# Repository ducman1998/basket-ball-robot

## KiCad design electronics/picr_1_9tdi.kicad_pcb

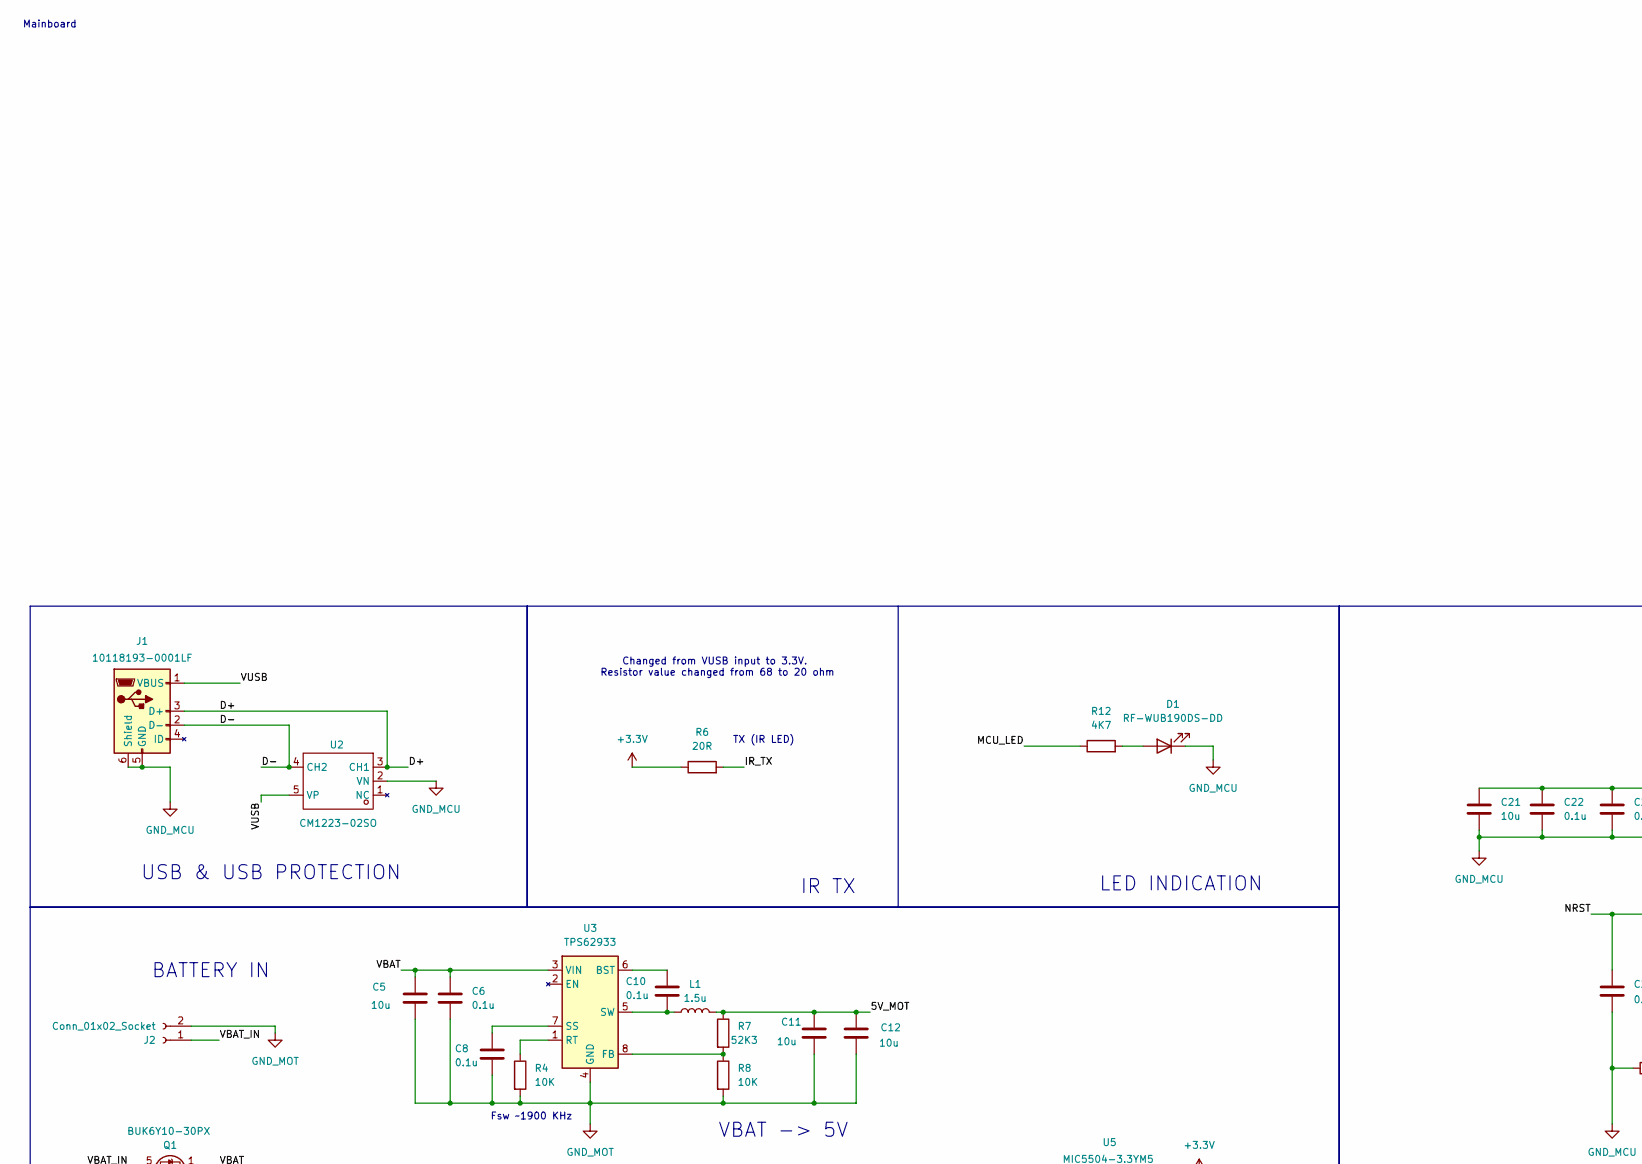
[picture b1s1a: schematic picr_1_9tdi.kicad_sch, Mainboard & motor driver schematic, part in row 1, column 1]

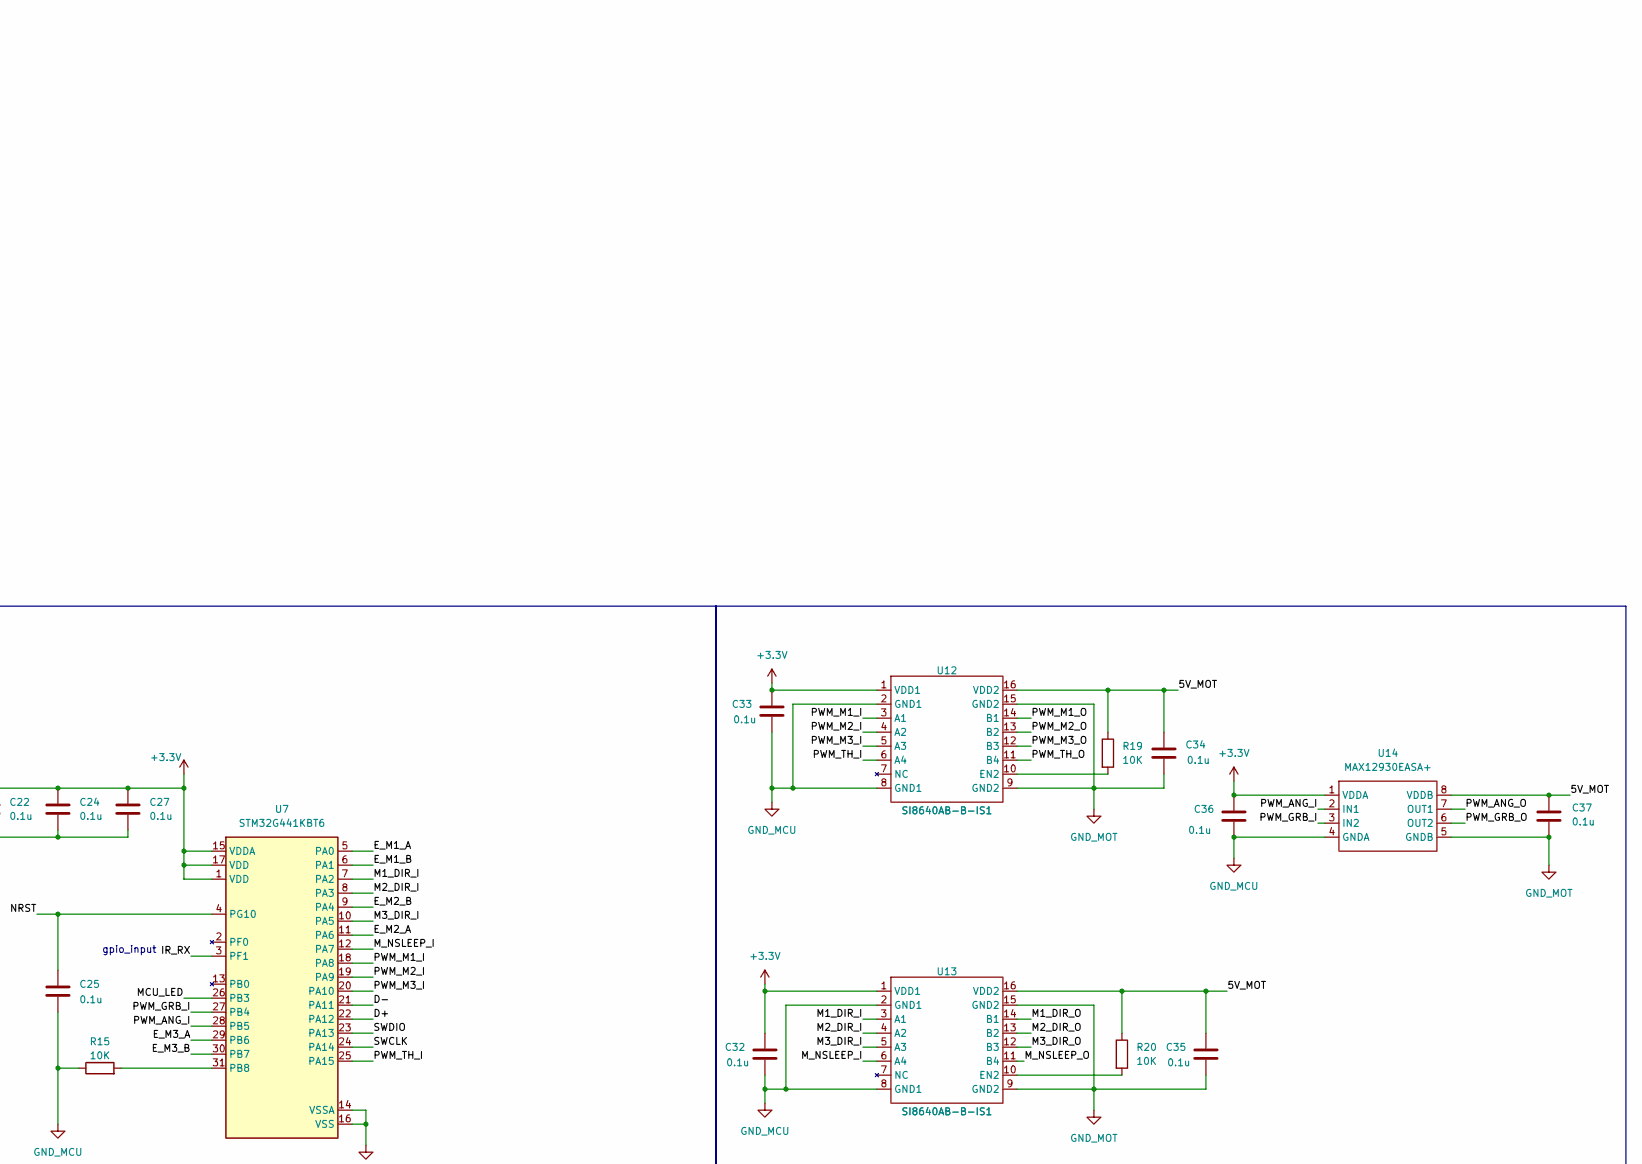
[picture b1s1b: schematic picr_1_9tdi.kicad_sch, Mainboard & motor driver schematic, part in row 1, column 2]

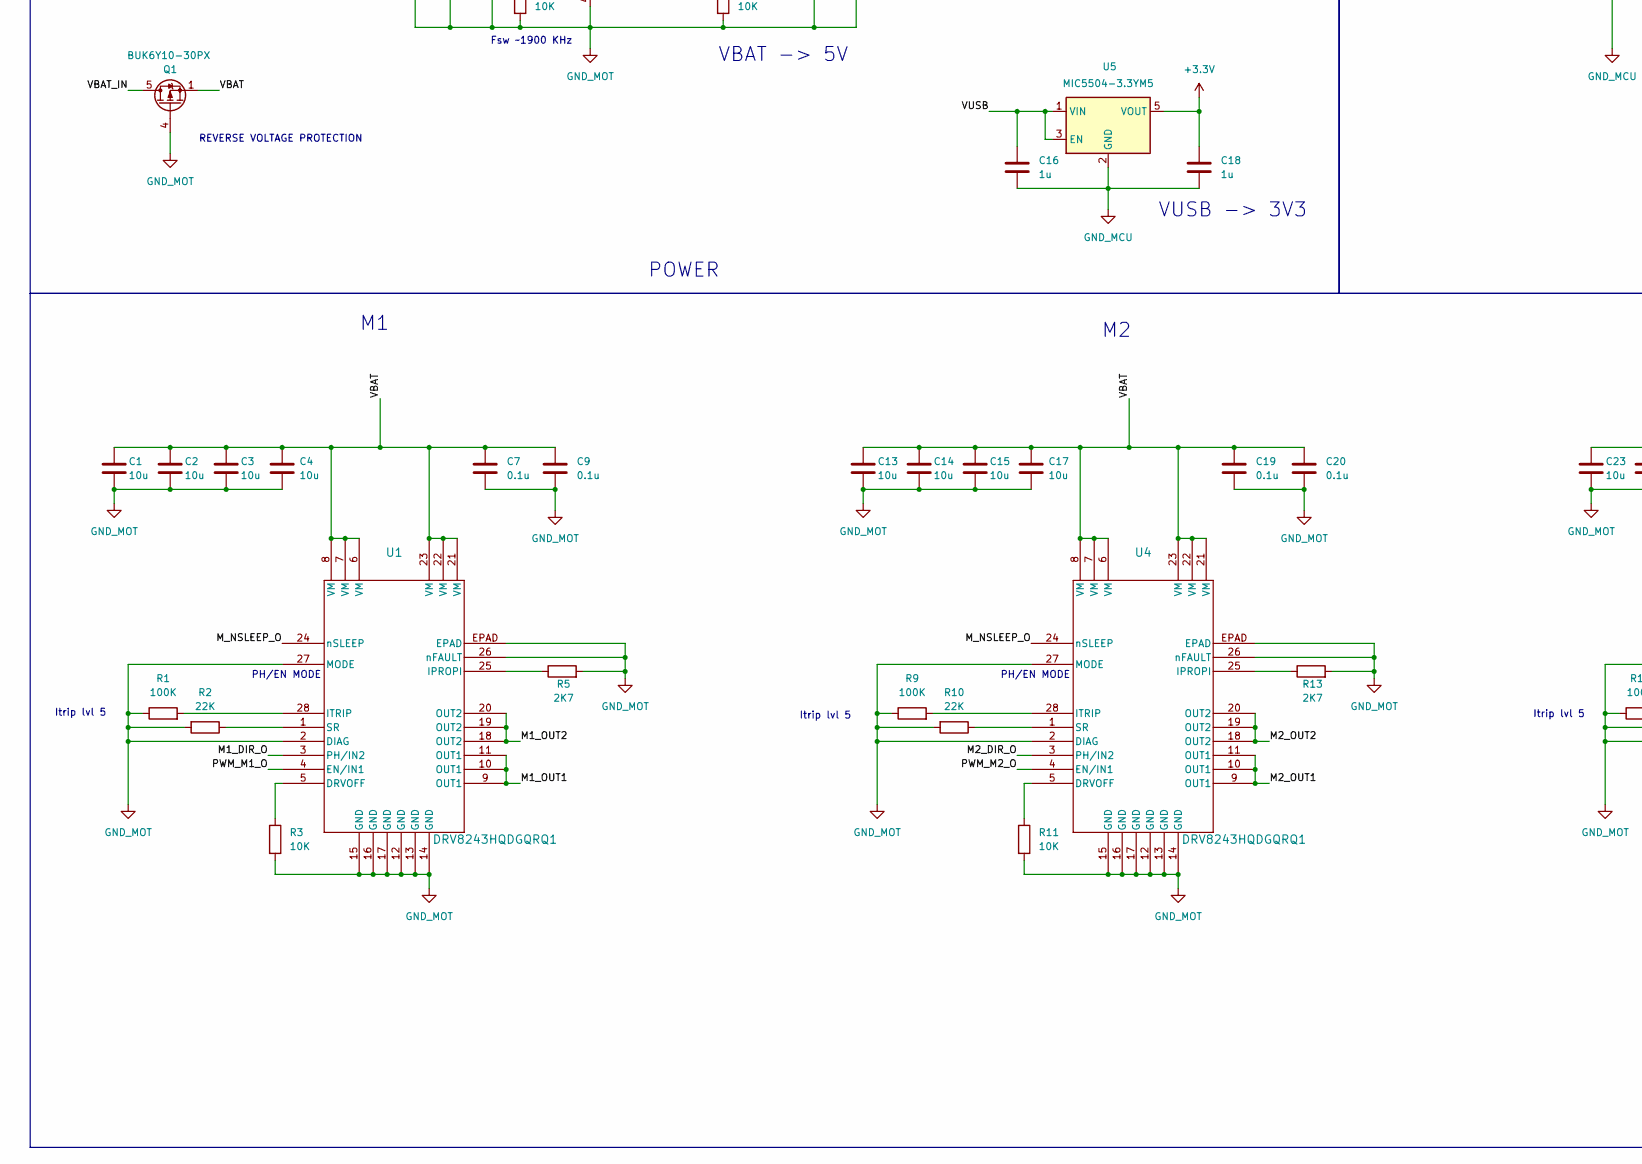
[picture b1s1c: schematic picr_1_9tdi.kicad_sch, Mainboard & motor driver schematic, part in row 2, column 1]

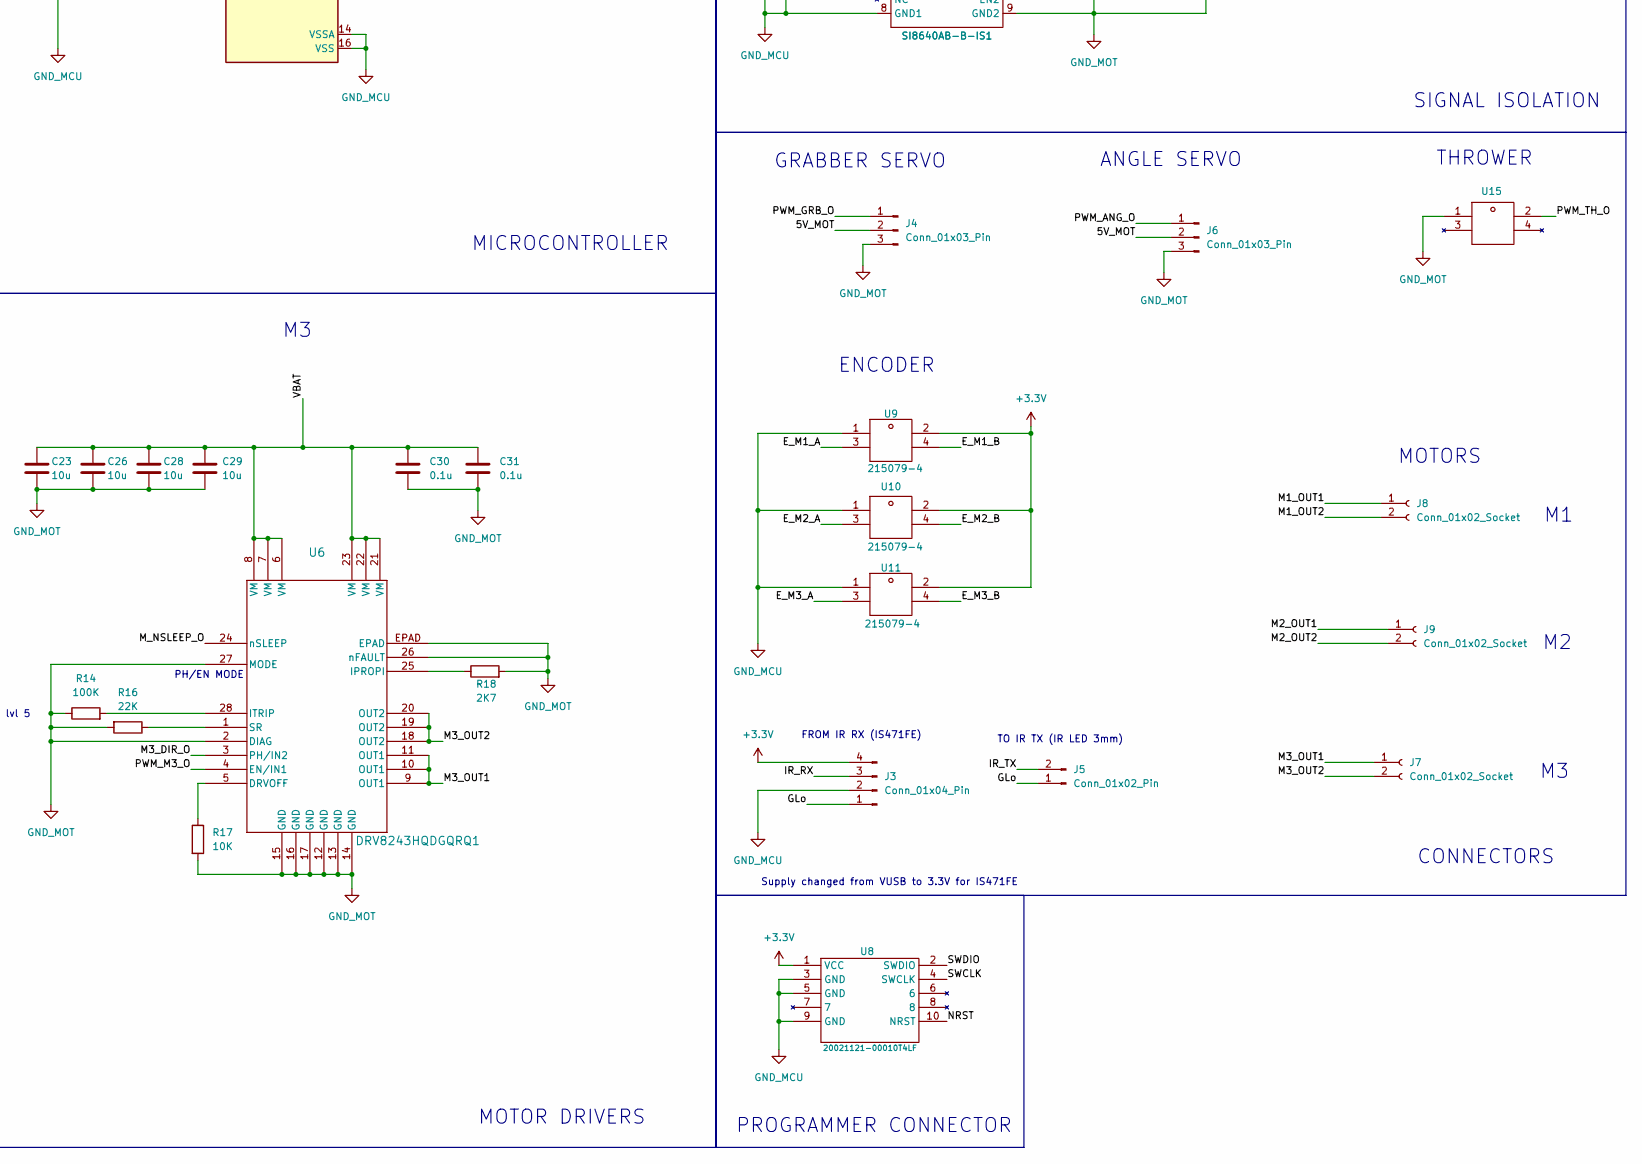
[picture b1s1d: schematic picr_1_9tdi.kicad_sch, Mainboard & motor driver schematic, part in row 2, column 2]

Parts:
C1, C2, C3, C4, C5, C13, C14, C15, C17, C21, C23, C26, C28, C29: 10u; C_0805_2012Metric_Pad1.18x1.45mm_HandSolder
C6, C7, C8, C9, C10, C19, C20, C22, C24, C25, C27, C30, C31, C32, C33, C34, C35, C36, C37: 0.1u; C_0603_1608Metric_Pad1.08x0.95mm_HandSolder
C11, C12: 10u; C_0603_1608Metric_Pad1.08x0.95mm_HandSolder
C16, C18: 1u; C_0603_1608Metric_Pad1.08x0.95mm_HandSolder
D1: RF-WUB190DS-DD; LED_0603_1608Metric_Pad1.05x0.95mm_HandSolder
J1: 10118193-0001LF; USB_Micro-B_Amphenol_10118193-0001LF_Horizontal
J2: Conn_01x02_Socket; SolderWirePad_1x02_SMD_3x4mm_power
J3: Conn_01x04_Pin; PinHeader_1x04_P2.54mm_Vertical
J4, J6: Conn_01x03_Pin; PinHeader_1x03_P2.54mm_Vertical
J5: Conn_01x02_Pin; PinHeader_1x02_P2.54mm_Vertical
J7, J8, J9: Conn_01x02_Socket; SolderWirePad_1x02_SMD_3x4mm
L1: 1.5u; SRP4021HMCT-1R5M_custom
Q1: BUK6Y10-30PX
R1, R9, R14: 100K; R_0603_1608Metric_Pad0.98x0.95mm_HandSolder
R2, R10, R16: 22K; R_0603_1608Metric_Pad0.98x0.95mm_HandSolder
R3, R4, R8, R11, R15, R17, R19, R20: 10K; R_0603_1608Metric_Pad0.98x0.95mm_HandSolder
R5, R13, R18: 2K7; R_0603_1608Metric_Pad0.98x0.95mm_HandSolder
R6: 20R; R_0603_1608Metric_Pad0.98x0.95mm_HandSolder
R7: 52K3; R_0603_1608Metric_Pad0.98x0.95mm_HandSolder
R12: 4K7; R_0603_1608Metric_Pad0.98x0.95mm_HandSolder
U1, U4, U6: DRV8243HQDGQRQ1; VSSOP_SDGQQ1_TEX-L
U2: CM1223-02SO; SOT-23-5_L2.9-W1.6-P0.95-LS2.8-BR; Manufacturer Part CM1223-02SO; LCSC Part Name CM1223-02SO
U3: TPS62933; SOT-583-8
U5: MIC5504-3.3YM5; SOT-23-5
U7: STM32G441KBT6; LQFP-32_7x7mm_P0.8mm
U8: 20021121-00010T4LF; HDR-SMD_10P-P1.27-V-M-R2-C5-S1.27-LS5.5; Manufacturer Part 20021121-00010T4LF; LCSC Part Name 间距:1.27mm 立贴
U9, U10, U11: 215079-4; TE_Micro-MaTch_215079-4_2x02_P1.27mm_Vertical; Manufacturer Part 215079-4; LCSC Part Name 215079-4
U12, U13: SI8640AB-B-IS1; Manufacturer Part SI8640AB-B-IS1; LCSC Part Name SI8640AB-B-IS1
U14: MAX12930EASA+; SOIC-8_L4.9-W3.9-P1.27-LS6.0-BL; Manufacturer Part MAX12930EASA+; LCSC Part Name MAX12930EASA+
U15: TE_Micro-MaTch_215079-4_2x02_P1.27mm_Vertical; Manufacturer Part 215079-4; LCSC Part Name 215079-4

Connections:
+3.3V: C18.1, C21.1, C22.1, C24.1, C27.1, C32.1, C33.1, C36.1, J3.4, R6.1, U5.5 (VOUT), U7.1 (VDD), U7.15 (VDDA), U7.17 (VDD), U8.1 (VCC), U9.2, U10.2, U11.2, U12.1 (VDD1), U13.1 (VDD1), U14.1 (VDDA)
/5V_MOT: C11.1, C12.1, C34.1, C35.1, C37.1, J4.2, J6.2, L1.2, R7.1, R19.1, R20.1, U12.16 (VDD2), U13.16 (VDD2), U14.8 (VDDB)
/D+: J1.3 (D+), U2.3 (CH1), U7.22 (PA12)
/D-: J1.2 (D-), U2.4 (CH2), U7.21 (PA11)
/E_M1_A: U7.5 (PA0), U9.3
/E_M1_B: U7.6 (PA1), U9.4
/E_M2_A: U7.11 (PA6), U10.3
/E_M2_B: U7.9 (PA4), U10.4
/E_M3_A: U7.29 (PB6), U11.3
/E_M3_B: U7.30 (PB7), U11.4
/GLo: J3.1, J5.1
/IR_RX: J3.3, U7.3 (PF1)
/IR_TX: J5.2, R6.2
/M1_DIR_I: U7.7 (PA2), U13.3 (A1)
/M1_DIR_O: U1.3 (PH/IN2), U13.14 (B1)
/M1_OUT1: J8.1, U1.9 (OUT1), U1.10 (OUT1), U1.11 (OUT1)
/M1_OUT2: J8.2, U1.18 (OUT2), U1.19 (OUT2), U1.20 (OUT2)
/M2_DIR_I: U7.8 (PA3), U13.4 (A2)
/M2_DIR_O: U4.3 (PH/IN2), U13.13 (B2)
/M2_OUT1: J9.1, U4.9 (OUT1), U4.10 (OUT1), U4.11 (OUT1)
/M2_OUT2: J9.2, U4.18 (OUT2), U4.19 (OUT2), U4.20 (OUT2)
/M3_DIR_I: U7.10 (PA5), U13.5 (A3)
/M3_DIR_O: U6.3 (PH/IN2), U13.12 (B3)
/M3_OUT1: J7.1, U6.9 (OUT1), U6.10 (OUT1), U6.11 (OUT1)
/M3_OUT2: J7.2, U6.18 (OUT2), U6.19 (OUT2), U6.20 (OUT2)
/MCU_LED: R12.1, U7.26 (PB3)
/M_NSLEEP_I: U7.12 (PA7), U13.6 (A4)
/M_NSLEEP_O: U1.24 (nSLEEP), U4.24 (nSLEEP), U6.24 (nSLEEP), U13.11 (B4)
/NRST: C25.1, U7.4 (PG10), U8.10 (NRST)
/PWM_ANG_I: U7.28 (PB5), U14.2 (IN1)
/PWM_ANG_O: J6.1, U14.7 (OUT1)
/PWM_GRB_I: U7.27 (PB4), U14.3 (IN2)
/PWM_GRB_O: J4.1, U14.6 (OUT2)
/PWM_M1_I: U7.18 (PA8), U12.3 (A1)
/PWM_M1_O: U1.4 (EN/IN1), U12.14 (B1)
/PWM_M2_I: U7.19 (PA9), U12.4 (A2)
/PWM_M2_O: U4.4 (EN/IN1), U12.13 (B2)
/PWM_M3_I: U7.20 (PA10), U12.5 (A3)
/PWM_M3_O: U6.4 (EN/IN1), U12.12 (B3)
/PWM_TH_I: U7.25 (PA15), U12.6 (A4)
/PWM_TH_O: U12.11 (B4), U15.2
/SWCLK: U7.24 (PA14), U8.4 (SWCLK)
/SWDIO: U7.23 (PA13), U8.2 (SWDIO)
/VBAT: C1.1, C2.1, C3.1, C4.1, C5.1, C6.1, C7.1, C9.1, C13.1, C14.1, C15.1, C17.1, C19.1, C20.1, C23.1, C26.1, C28.1, C29.1, C30.1, C31.1, Q1.1 (S), Q1.2 (S), Q1.3 (S), U1.6 (VM), U1.7 (VM), U1.8 (VM), U1.21 (VM), U1.22 (VM), U1.23 (VM), U3.3 (VIN), U4.6 (VM), U4.7 (VM), U4.8 (VM), U4.21 (VM), U4.22 (VM), U4.23 (VM), U6.6 (VM), U6.7 (VM), U6.8 (VM), U6.21 (VM), U6.22 (VM), U6.23 (VM)
/VBAT_IN: J2.1, Q1.5 (D)
/VUSB: C16.1, J1.1 (VBUS), U2.5 (VP), U5.1 (VIN), U5.3 (EN)
GND_MCU: C16.2, C18.2, C21.2, C22.2, C24.2, C25.2, C27.2, C32.2, C33.2, C36.2, D1.1 (K), J1.5 (GND), J1.6 (Shield), J3.2, R15.1, U2.2 (VN), U5.2 (GND), U7.14 (VSSA), U7.16 (VSS), U7.32 (VSS), U8.3 (GND), U8.5 (GND), U8.9 (GND), U9.1, U10.1, U11.1, U12.2 (GND1), U12.8 (GND1), U13.2 (GND1), U13.8 (GND1), U14.4 (GNDA)
GND_MOT: C1.2, C2.2, C3.2, C4.2, C5.2, C6.2, C7.2, C8.2, C9.2, C11.2, C12.2, C13.2, C14.2, C15.2, C17.2, C19.2, C20.2, C23.2, C26.2, C28.2, C29.2, C30.2, C31.2, C34.2, C35.2, C37.2, J2.2, J4.3, J6.3, Q1.4 (G), R1.1, R2.2, R3.2, R4.2, R5.2, R8.2, R9.1, R10.2, R11.2, R13.2, R14.1, R16.2, R17.2, R18.2, U1.2 (DIAG), U1.12 (GND), U1.13 (GND), U1.14 (GND), U1.15 (GND), U1.16 (GND), U1.17 (GND), U1.26 (nFAULT), U1.27 (MODE), U1.EPAD, U3.4 (GND), U4.2 (DIAG), U4.12 (GND), U4.13 (GND), U4.14 (GND), U4.15 (GND), U4.16 (GND), U4.17 (GND), U4.26 (nFAULT), U4.27 (MODE), U4.EPAD, U6.2 (DIAG), U6.12 (GND), U6.13 (GND), U6.14 (GND), U6.15 (GND), U6.16 (GND), U6.17 (GND), U6.26 (nFAULT), U6.27 (MODE), U6.EPAD, U12.9 (GND2), U12.15 (GND2), U13.9 (GND2), U13.15 (GND2), U14.5 (GNDB), U15.1
unnamed: D1.2 (A), R12.2
unnamed: R3.1, U1.5 (DRVOFF)
unnamed: R5.1, U1.25 (IPROPI)
unnamed: R1.2, U1.28 (ITRIP)
unnamed: R2.1, U1.1 (SR)
unnamed: C10.1, U3.6 (BST)
unnamed: R7.2, R8.1, U3.8 (FB)
unnamed: R4.1, U3.1 (RT)
unnamed: C8.1, U3.7 (SS)
unnamed: C10.2, L1.1, U3.5 (SW)
unnamed: R11.1, U4.5 (DRVOFF)
unnamed: R13.1, U4.25 (IPROPI)
unnamed: R9.2, U4.28 (ITRIP)
unnamed: R10.1, U4.1 (SR)
unnamed: R17.1, U6.5 (DRVOFF)
unnamed: R18.1, U6.25 (IPROPI)
unnamed: R14.2, U6.28 (ITRIP)
unnamed: R16.1, U6.1 (SR)
unnamed: R15.2, U7.31 (PB8)
unnamed: R19.2, U12.10 (EN2)
unnamed: R20.2, U13.10 (EN2)

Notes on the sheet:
PH/EN MODE
VUSB -> 3V3
THROWER
TO IR TX (IR LED 3mm)
Fsw ~1900 KHz
Itrip lvl 5
Supply changed from VUSB to 3.3V for IS471FE
gpio_input
GRABBER SERVO
POWER
VBAT -> 5V
REVERSE VOLTAGE PROTECTION
ANGLE SERVO
ENCODER
MOTOR DRIVERS
PROGRAMMER CONNECTOR
LED INDICATION
SIGNAL ISOLATION
IR TX
MOTORS
TX (IR LED)
FROM IR RX (IS471FE)
Changed from VUSB input to 3.3V. Resistor value changed from 68 to 20 ohm
MICROCONTROLLER
CONNECTORS
Mainboard
BATTERY IN
USB & USB PROTECTION

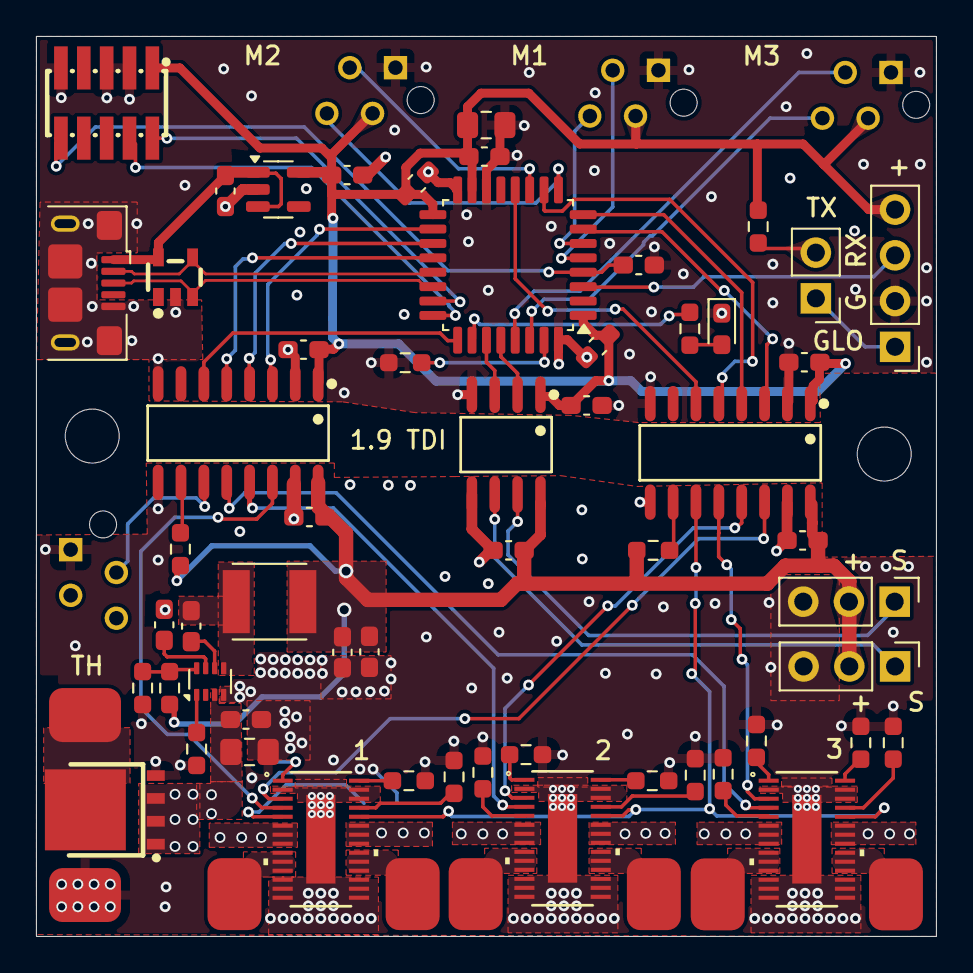
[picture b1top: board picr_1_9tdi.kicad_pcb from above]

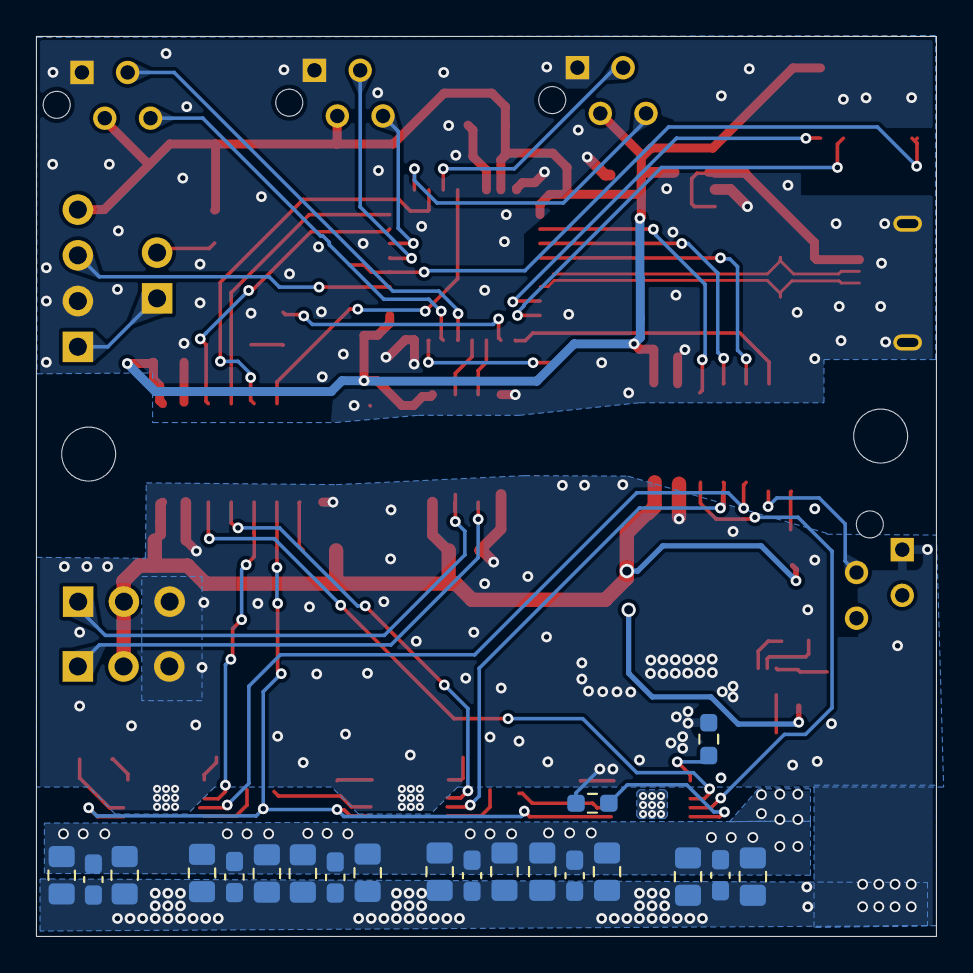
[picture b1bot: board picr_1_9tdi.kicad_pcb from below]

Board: 4 copper layers, 50.0 x 50.0 mm, 84 parts (20 on the bottom side), 69 nets.

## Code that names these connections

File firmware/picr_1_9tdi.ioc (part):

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Mcu.Name=STM32G441KBTx
Mcu.Package=LQFP32
Mcu.UserName=STM32G441KBTx
PA0.GPIOParameters=GPIO_Label
PA0.GPIO_Label=E_M1_A
PA0.Signal=S_TIM2_CH1
PA1.GPIOParameters=GPIO_Label
PA1.GPIO_Label=E_M1_B
PA1.Signal=S_TIM2_CH2
PA10.GPIOParameters=GPIO_Label
PA10.GPIO_Label=PWM_M3
PA10.Signal=S_TIM1_CH3
PA11.Mode=Device
PA11.Signal=USB_DM
PA12.Mode=Device
PA12.Signal=USB_DP
PA13.Mode=Serial_Wire
PA13.Signal=SYS_JTMS-SWDIO
PA14.Mode=Serial_Wire
PA14.Signal=SYS_JTCK-SWCLK
PA15.GPIOParameters=GPIO_Label
PA15.GPIO_Label=PWM_TH
PA15.Signal=S_TIM8_CH1
PA2.GPIOParameters=GPIO_Label
PA2.GPIO_Label=M1_DIR
PA2.Signal=GPIO_Output
PA3.GPIOParameters=GPIO_Label
PA3.GPIO_Label=M2_DIR
PA3.Signal=GPIO_Output
PA4.GPIOParameters=GPIO_Label
PA4.GPIO_Label=E_M2_B
PA4.Signal=S_TIM3_CH2
PA5.GPIOParameters=GPIO_Label
PA5.GPIO_Label=M3_DIR
PA5.Signal=GPIO_Output
PA6.GPIOParameters=GPIO_Label
PA6.GPIO_Label=E_M2_A
PA6.Signal=S_TIM3_CH1
PA7.GPIOParameters=GPIO_Label
PA7.GPIO_Label=NSLEEP
PA7.Signal=GPIO_Output
PA8.GPIOParameters=GPIO_Label
PA8.GPIO_Label=PWM_M1
PA8.Signal=S_TIM1_CH1
PA9.GPIOParameters=GPIO_Label
PA9.GPIO_Label=PWM_M2
PA9.Signal=S_TIM1_CH2
PB3.GPIOParameters=GPIO_Label
PB3.GPIO_Label=MCU_LED
PB3.Signal=GPIO_Output
PB4.GPIOParameters=GPIO_Label
PB4.GPIO_Label=PWM_GRB
PB4.Signal=S_TIM16_CH1
PB5.GPIOParameters=GPIO_Label
PB5.GPIO_Label=PWM_ANG
PB5.Signal=S_TIM17_CH1
PB6.GPIOParameters=GPIO_Label
PB6.GPIO_Label=E_M3_A
PB6.Signal=S_TIM4_CH1
PB7.GPIOParameters=GPIO_Label
PB7.GPIO_Label=E_M3_B
PB7.Signal=S_TIM4_CH2
PF1-OSC_OUT.GPIOParameters=GPIO_Label
PF1-OSC_OUT.GPIO_Label=IR_RX
PF1-OSC_OUT.Mode=IN10-Single-Ended
PF1-OSC_OUT.Signal=ADC2_IN10
RCC.HSE_VALUE=8000000
RCC.SYSCLKFreq_VALUE=160000000
RCC.SYSCLKSource=RCC_SYSCLKSOURCE_PLLCLK
board=custom

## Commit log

2025-09-06 Init main
2025-09-06 Create software README
2025-09-06 Create electronics README
2025-09-06 Create firmware README
2025-09-17 Added team members
2025-09-17 Added task spreadsheet
2025-09-17 Added camera extrinsic calibration notebook
2025-09-17 Structure repo
2025-09-17 Update team name
2025-09-17 Reorgranize folder structure
2025-09-18 Added robot ommiwheel kinematics + mainboard communication
2025-09-18 Added documentation
2025-09-18 Update var names
2025-09-18 Refactored code + added config file
2025-09-19 Added auto-scan serial port based on hardware ID
2025-09-19 Update code
2025-09-19 Updated disable_failsafe to boolean in test code
2025-09-20 Updated exception handler in config util & requirements
2025-09-20 Added formater + linter
2025-09-20 Add pre-commit hooks for code checking + minor updates on code to meet code quality
2025-09-20 Change *_util to _utils as a standard
2025-09-20 Code format
2025-09-20 Updated cam calibration doc
2025-09-22 Format code + change conf var name to lowercase
2025-09-22 Update name of H to jacobian
2025-09-25 Add teleop + mainboard controller nodes
2025-09-26 Implemented Odometry node + modified base-controller node
2025-09-26 Updated documents for Odometry + Mainboard controller
2025-09-26 Updated document robot controller
2025-09-26 Updated robot control document
2025-09-26 Updated document for teleop node
2025-09-27 Updated Jacobian + Odometry logic
2025-09-27 Updated Edit ODOMETRY.asciidoc
2025-09-28 Deleted empty scripts
2025-09-28 Removed default parameters in OmmiMotionRobot class, only robot params read from yaml in launch file is used to init OmmiMotionRobot
2025-09-29 Edited robot.launch.py
2025-09-30 Upload New File
2025-09-30 Add new file
2025-10-01 Schem rev1
2025-10-01 Edit .gitignore
2025-10-04 Schem rev2
2025-10-05 Added robot-finds-a-ball launch file and game-logic controller for it (image processor, etc)
2025-10-05 Updated game logic
2025-10-05 Fixed logic error in image-processor node
2025-10-05 Updated code based on field test
2025-10-05 Added multiple reference ball colors to improve ball detection accurary
2025-10-05 Updated document
2025-10-05 Removed duplidate (move robot 2 times) in REACHING_BALL state
2025-10-05 Removed an unnecessary constant
2025-10-06 Updated PID params
2025-10-07 Schem rev3
2025-10-08 Updated comment
2025-10-09 Updated code to meet MR comments
2025-10-09 Added norm step before sending cmd-vel to mainboard-controller node
2025-10-09 Changed print to logger.info
2025-10-11 Improved ball detection algorithm + Set a fixed exposure time for color cam
2025-10-11 Update 23 files
    - /electronics/picr_1_9tdi-backups/picr_1_9tdi-2025-09-23_205805/picr_1_9tdi.kicad_pcb
    - /electronics/picr_1_9tdi-backups/picr_1_9tdi-2025-09-23_205805/picr_1_9tdi.kicad_prl
    - /electronics/picr_1_9tdi-backups/picr_1_9tdi-2025-09-23_205805/picr_1_9tdi.kicad_pro
    - /electronics/picr_1_9tdi-backups/picr_1_9tdi-2025-09-23_205805/picr_1_9tdi.kicad_sch
    - /electronics/picr_1_9tdi-backups/picr_1_9tdi-2025-09-23_205805/untitled.kicad_sch
    - /electronics/picr_1_9tdi-backups/picr_1_9tdi-2025-10-07_171026.zip
2025-10-12 Added more ref colors for green ball detection
2025-10-12 Updated ball detection alg / Off auto white balance
2025-10-14 Added robot-find-a-ball task logic, tighten ball detection threshold
2025-10-15 Updated game logic controller based on experiments
2025-10-19 Refactored ros setting.yaml and related launch files to pass setting filepath instead of a dictionary
2025-10-20 Revert "Merge branch 'robot_follow_a_ball' into 'software'"
    This reverts merge request !3
2025-10-21 Change code logic + image processing thresholds (not done yet)
2025-10-22 Updated game logic: robot will reach court center if no ball detected during searching state
2025-10-22 Updated game logic + image processing thresholds/logics
2025-10-22 Revert "Revert "Merge branch 'robot_follow_a_ball' into 'software'""
    This reverts commit 85a2163ec675d8f5c9c19424805a44d39aa4db20.
2025-10-23 Fixed comments from Allan
2025-10-23 Added code to rotate the robot around the detected ball
2025-10-26 A rudimentary example on how to use the segmentation module to segment all colors at once. The configurator should either be integrated into a separate node or used as an external tool. Should not st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
    Pay attention to image_processor.COLOR_CONF to pass the correct color configuration to.
2025-10-28 Changed image processing pipeline to use a color segmentor, updated game logic
2025-10-29 Speedup image processing, updated game logic based on experiment
2025-10-29 Updated function docstring
2025-10-31 Refactored PID params
2025-11-03 Refactored code to meed quality reviews
2025-11-06 Updated code to meet quality review
2025-11-11 Replace 0.2/0.4 vias with 0.2/0.45 vias and adjust GND copper zone
2025-11-12 Updated game logic to well-aligned to the basket when throwing the ball | Added websocket client to receive cmd from referee server
2025-11-17 Updated code to meed quality reviews
2025-11-17 Added Timeout Exception
2025-11-19 Updated new code logic (angle threshold variable, calib thrower percent)
2025-11-20 Updated team ID for competitioin
2025-11-30 Speedup segmentation with numba, improved detection (ball & basket), updated for new robot
2025-11-30 In progress work (todo)
2025-12-09 Added marker detection + optimized perception pipeline
2025-12-10 Refactor game logic into base & manipulation handlers (in-progress)
2025-12-10 Sampling move-xy target into multiple sub-target following the straigh line
2025-12-10 Turn to pure-persuit look-like controller to force robot follow straight line (not work well, better than previous commit)
2025-12-11 Implemented manipulation handlers (loading 80%, needs testing)
2025-12-11 Modified logic based on experiments
2025-12-11 Finish state-machine (needs testing)
2025-12-11 Removed unsed settings
2025-12-11 Removed unsed code
2025-12-12 Added advanced basket alignment state to state-machine
2025-12-12 Bug fix: updated threshold for advanced baasket alignment
2025-12-12 Updated code
2025-12-12 Turn the basket 2d position from depth to markers based if possible
2025-12-12 Ensure enough time for aligning robot towards basket (dampen angle error) before throwing in advanced basket alignment
2025-12-12 Get rid of turn-continuous sub-state to speedup search process
2025-12-13 Changed advanced basket alignment to use both markers (mean their poses)
2025-12-13 Fixed bug: basket alignment based on experimental offset
2025-12-13 Speedup program by tuning time related parameters
2025-12-13 Set the distance to basket the same as current distanct to basket
2025-12-15 Clean state-machine, added ball-manager to store detected balls in odom frame
2025-12-15 Updated parameters based on experiment
2025-12-15 Updated parameters and code
2025-12-15 Updated new calib thrower speed + fixed bug: robot ran behind the basket
2025-12-15 edit comment
2025-12-18 Updated with new partial calibration
2025-12-18 Apply 1 suggestion(s) to 1 file(s)
2025-12-18 Updated code for competition
2025-12-23 Updated parameters to speed up the robot
2025-12-25 Added checking if ball is inside or outside of the court
2025-12-25 Refactored thrower moter percent mapping to constant file
2026-01-08 Updated new parameters
2026-01-10 Calibrated thrower percent + basket offset (finished)
2026-01-10 Updated parameters + Added speed norm to align ball/basket_adv to speedup
2026-01-11 Update parameters | Slow down the robot when no basket found
2026-01-16 Updated parameters based on competition
2026-01-16 Changed advanced basket alignment to align by only position (set R=I)
2026-01-16 Recalibrated lateral distance offset to basket
2026-01-16 Updated parameters based on test competition
2026-01-19 Finished final documenatioin
2026-03-18 Update documentation
2026-03-18 Update interactive mechanics design
2026-06-02 Add demo video link to README
    Added a link to the demo video in the README.
2026-06-02 Update demo link to final game in README
2026-06-02 Fix duplicate link in README
    Removed duplicate link to the final game and adjusted formatting.
2026-06-02 Enhance README with video and image links
    Added links to the final game video and images of the robot and fusion design.
2026-06-02 Format link to watch the final game in bold
